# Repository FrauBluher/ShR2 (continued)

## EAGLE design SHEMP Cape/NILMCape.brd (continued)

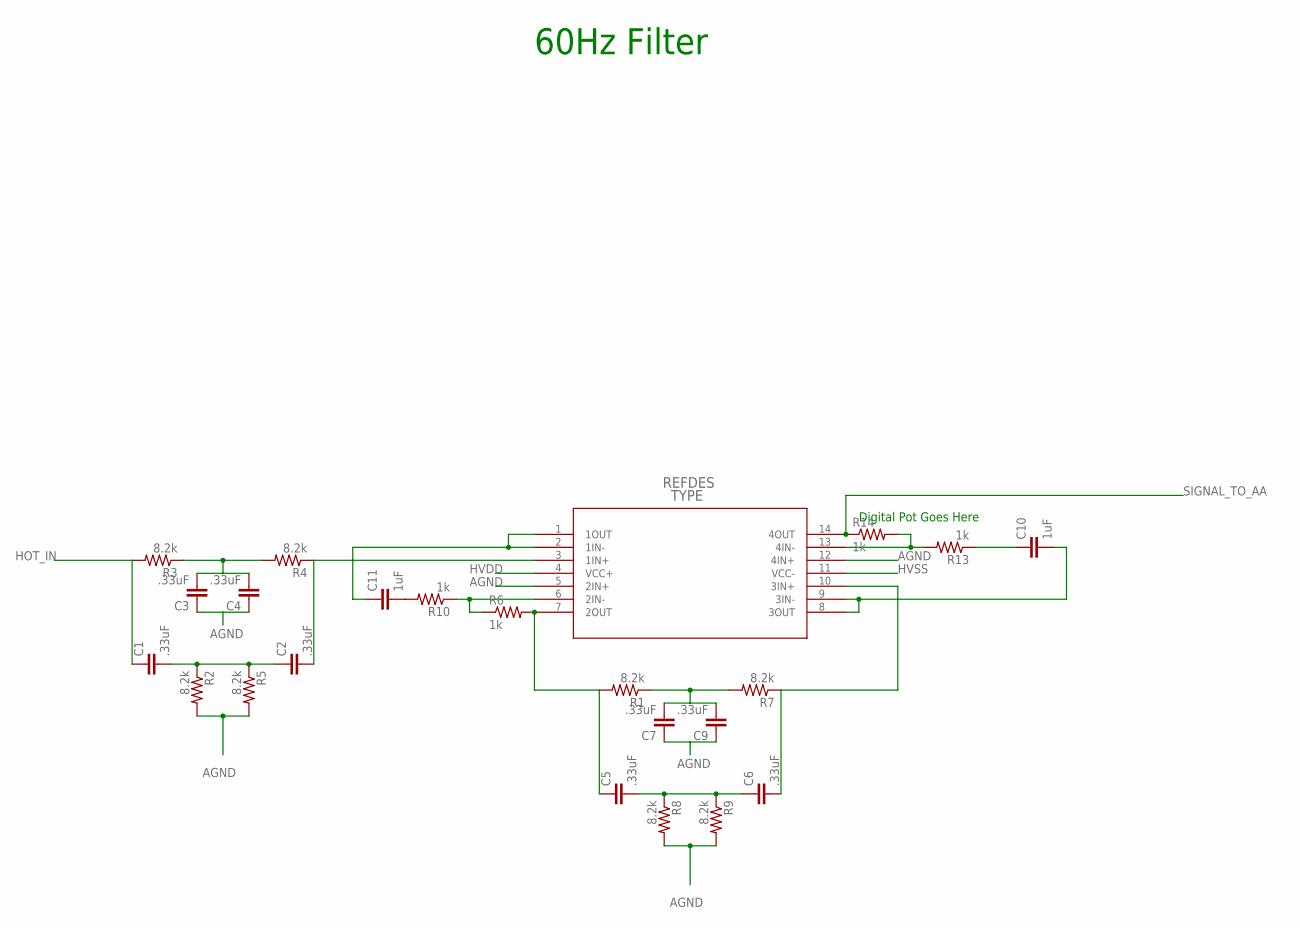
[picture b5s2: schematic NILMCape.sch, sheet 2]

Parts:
C1, C2, C3, C4, C5, C6, C7, C9: .33uF; 0805
C10, C11: 1uF; 0805
R1, R2, R3, R4, R5, R7, R8, R9: 8.2k; 0805
R6, R10, R13, R14: 1k; 0805
U9: TL074_PW_14; PW14

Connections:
AGND: C3.1, C4.1, C7.1, C9.1, R2.2, R5.2, R8.2, R9.2, U9.5 (2IN+), U9.12 (4IN+)
HOT_IN: C1.1, R3.2
HVDD: U9.4 (VCC+)
HVSS: U9.11 (VCC-); also elsewhere on the board
unnamed: C5.1, R1.2, R6.2, U9.7 (2OUT)
unnamed: C1.2, C2.1, R2.1, R5.1
unnamed: C3.2, C4.2, R3.1, R4.2
unnamed: R6.1, R10.1, U9.6 (2IN-)
unnamed: C2.2, R4.1, U9.3 (1IN+)
unnamed: C5.2, C6.1, R8.1, R9.1
unnamed: C7.2, C9.2, R1.1, R7.2
unnamed: C6.2, R7.1, U9.10 (3IN+)
unnamed: C10.2, U9.8 (3OUT), U9.9 (3IN-)
unnamed: R13.2, R14.2, U9.13 (4IN-)
unnamed: C10.1, R13.1
unnamed: C11.2, R10.2
unnamed: C11.1, U9.1 (1OUT), U9.2 (1IN-)
SIGNAL_TO_AA: R14.1, U9.14 (4OUT)

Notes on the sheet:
60Hz Filter
Digital Pot Goes Here

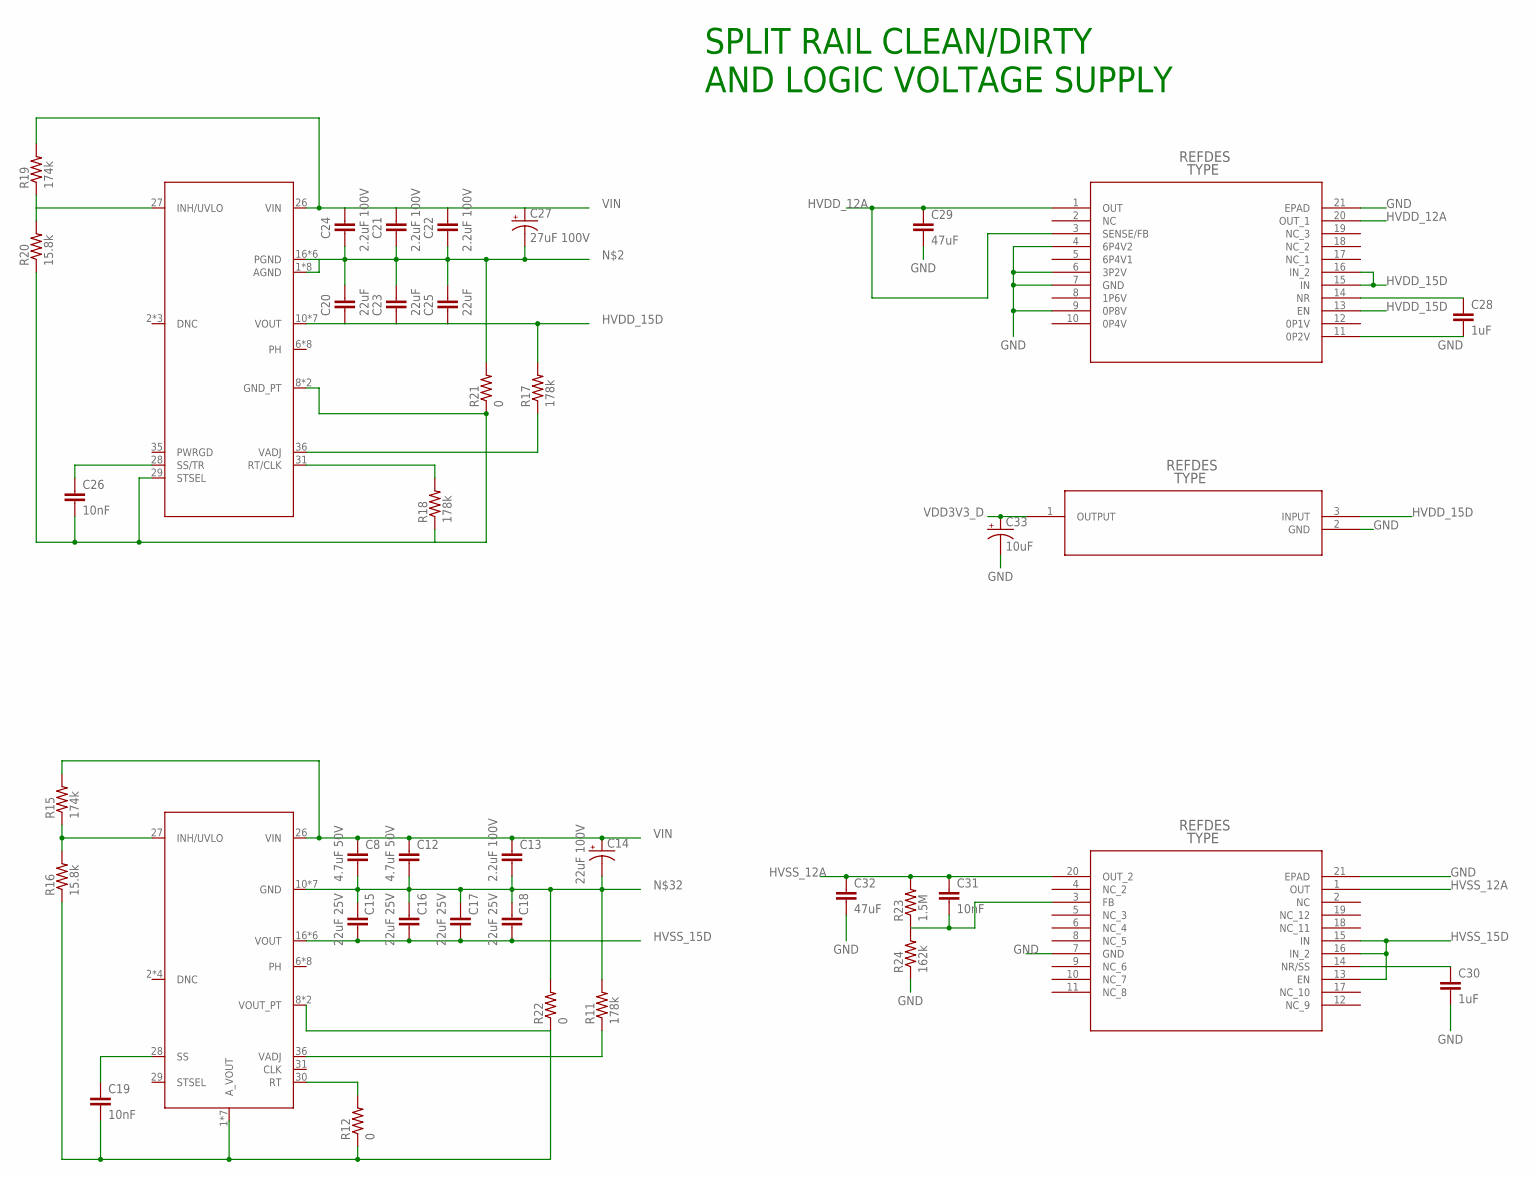
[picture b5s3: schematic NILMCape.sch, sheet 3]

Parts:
C8, C12: 4.7uF 50V; 1210
C13, C21, C22, C24: 2.2uF 100V; 1210
C14: 22uF 100V; CPOL-RADIAL-100UF-25V
C15, C16, C17, C18: 22uF 25V; 1210
C19, C26, C31: 10nF; 0805
C20, C23, C25: 22uF; 1210
C27: 27uF 100V; CPOL-RADIAL-100UF-25V
C28, C30: 1uF; 0805
C29, C32: 47uF; 1210
C33: 10uF; CPOL-RADIAL-10UF-25V
R11, R17, R18: 178k; 0805
R12, R21, R22: 0; 0805
R15, R19: 174k; 0805
R16, R20: 15.8k; 0805
R23: 1.5M; 0805
R24: 162k; 0805
U5: TPS84250_RKG_41; RKG41
U6: TPS7A3301_RGW_20; RGW20_3P15X3P15
U7: LP2950-33_KVU_3; KVU3
U$2: TPS84259_RKG_41; RKG41
U$3: TPS7A4700_RGW_20; RGW20_3P15X3P15

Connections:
GND: C19.2, C28.2, C29.2, C30.2, C32.2, C33.2 (-), R12.1, R16.1, R22.1, R24.1, U6.7 (GND), U6.21 (EPAD), U7.2 (GND), U$2.1 (A_VOUT), U$2.4 (A_VOUT), U$2.5 (A_VOUT), U$2.8 (VOUT_PT), U$2.9 (VOUT_PT), U$2.32 (A_VOUT), U$2.33 (A_VOUT), U$2.34 (A_VOUT), U$2.37 (A_VOUT), U$3.4 (6P4V2), U$3.6 (3P2V), U$3.7 (GND), U$3.9 (0P8V), U$3.11 (0P2V), U$3.21 (EPAD); also elsewhere on the board
HVDD_12A: C29.1, U$3.1 (OUT), U$3.3 (SENSE/FB), U$3.20 (OUT_1)
HVDD_15D: C20.2, C23.2, C25.2, R17.2, U5.10 (VOUT), U5.11 (VOUT), U5.12 (VOUT), U5.13 (VOUT), U5.14 (VOUT), U5.15 (VOUT), U5.39 (VOUT), U7.3 (INPUT), U$3.13 (EN), U$3.15 (IN), U$3.16 (IN_2)
HVSS_12A: C31.1, C32.1, R23.2, U6.1 (OUT), U6.20 (OUT_2)
HVSS_15D: C15.2, C16.2, C17.2, C18.2, U6.13 (EN), U6.15 (IN), U6.16 (IN_2), U$2.16 (VOUT), U$2.17 (VOUT), U$2.18 (VOUT), U$2.19 (VOUT), U$2.20 (VOUT), U$2.40 (VOUT)
unnamed: C20.1, C21.2, C22.2, C23.1, C24.2, C25.1, C27.2 (-), R21.2, U5.1 (AGND), U5.4 (AGND), U5.5 (AGND), U5.16 (PGND), U5.17 (PGND), U5.18 (PGND), U5.19 (PGND), U5.20 (PGND), U5.30 (AGND), U5.32 (AGND), U5.33 (AGND), U5.34 (AGND), U5.37 (AGND), U5.40 (PGND)
unnamed: C19.1, U$2.28 (SS)
unnamed: C31.2, R24.2, U6.3 (FB)
unnamed: R11.1, U$2.36 (VADJ)
unnamed: R12.2, U$2.30 (RT)
unnamed: C8.2, C12.2, C13.2, C14.2 (-), C15.1, C16.1, C17.1, C18.1, R11.2, R22.2, U$2.10 (GND), U$2.11 (GND), U$2.12 (GND), U$2.13 (GND), U$2.14 (GND), U$2.15 (GND), U$2.39 (GND)
unnamed: C30.1, U6.14 (NR/SS)
unnamed: R15.1, R16.2, U$2.27 (INH/UVLO)
unnamed: R17.1, U5.36 (VADJ)
unnamed: R18.2, U5.31 (RT/CLK)
unnamed: R19.1, R20.2, U5.27 (INH/UVLO)
unnamed: C26.1, U5.28 (SS/TR)
unnamed: C26.2, R18.1, R20.1, R21.1, U5.8 (GND_PT), U5.9 (GND_PT), U5.29 (STSEL)
unnamed: C28.1, U$3.14 (NR)
VDD3V3_D: C33.1 (+), U7.1 (OUTPUT); also elsewhere on the board
VIN: C8.1, C12.1, C13.1, C14.1 (+), C21.1, C22.1, C24.1, C27.1 (+), R15.2, R19.2, U5.26 (VIN), U$2.26 (VIN)

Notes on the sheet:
SPLIT RAIL CLEAN/DIRTY AND LOGIC VOLTAGE SUPPLY

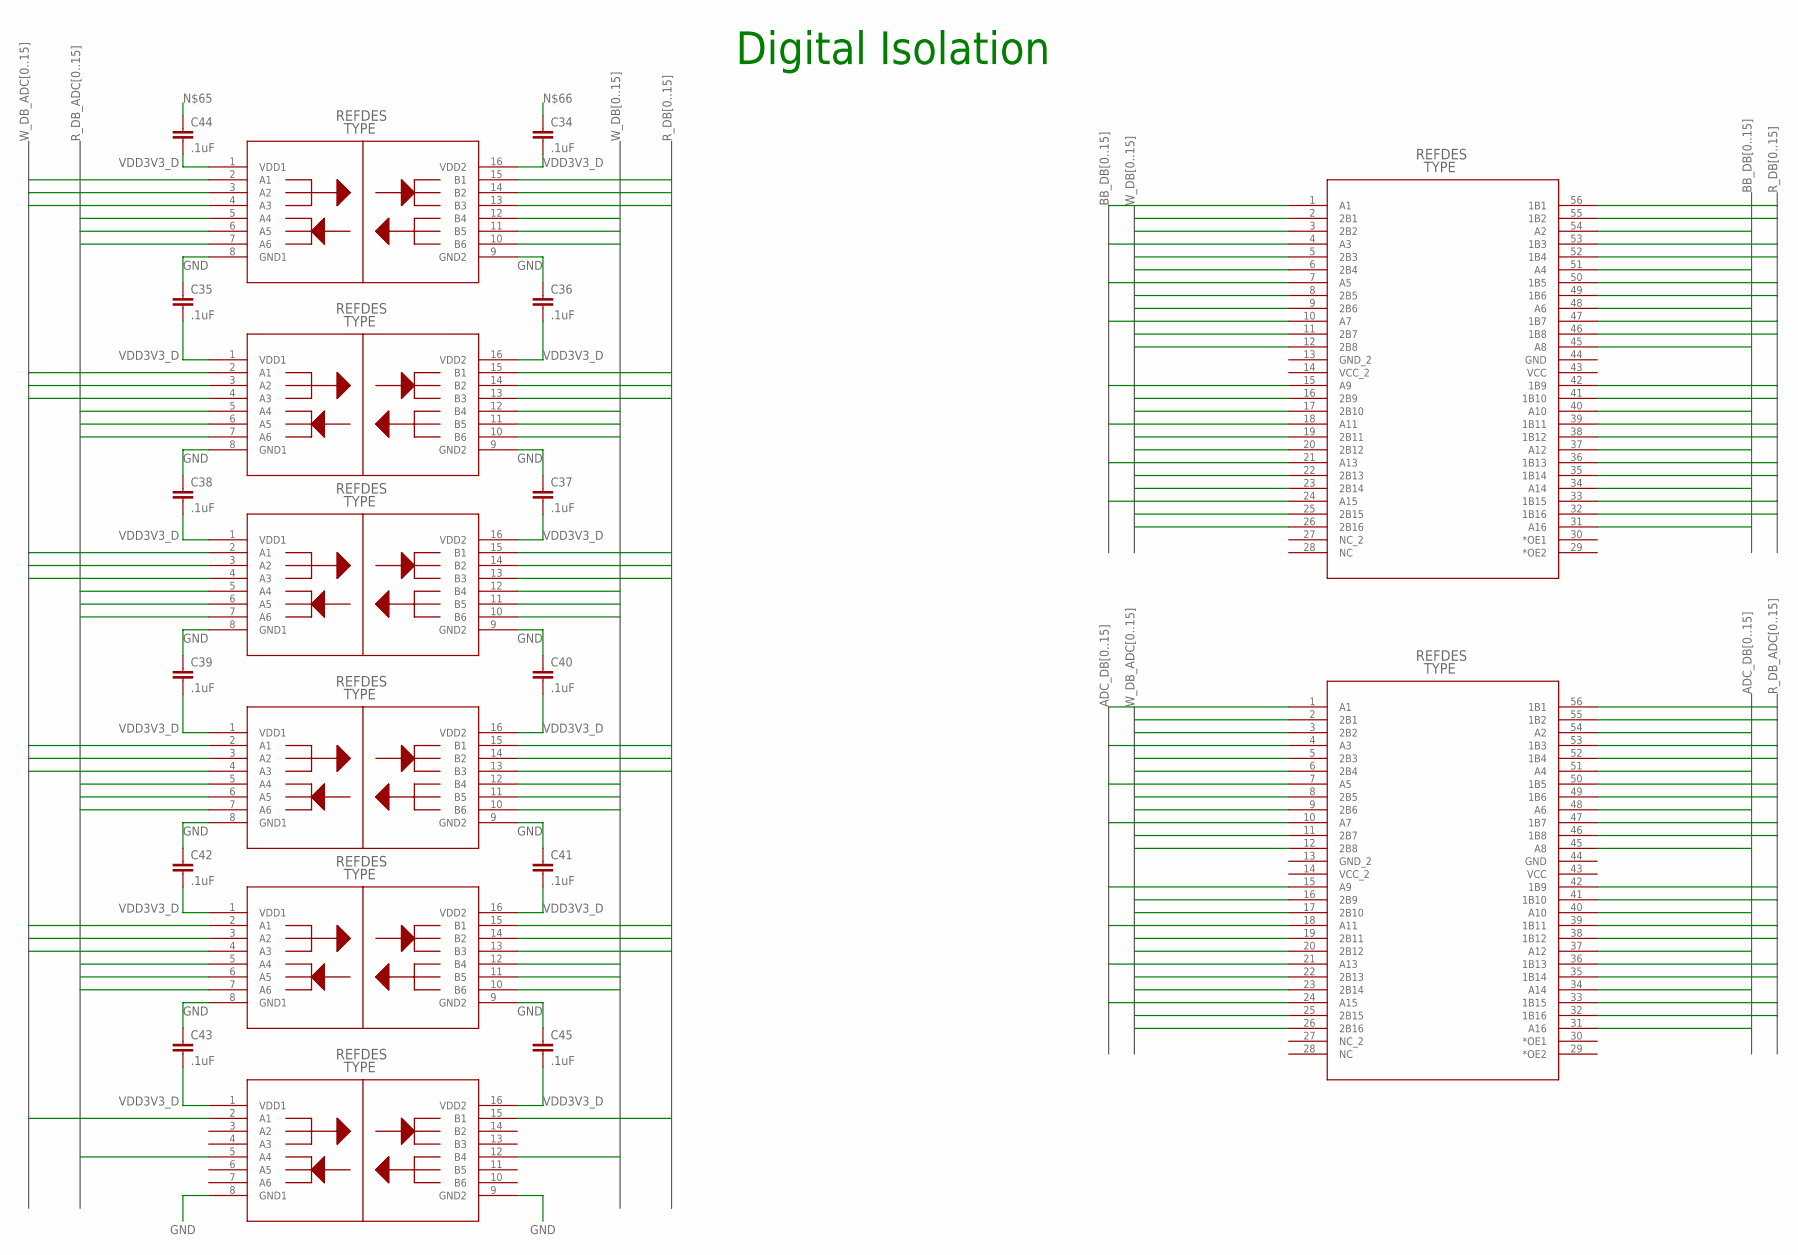
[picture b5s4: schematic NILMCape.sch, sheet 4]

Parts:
C34, C35, C36, C37, C38, C39, C40, C41, C42, C43, C44, C45: .1uF; 0805
U3, U8, U10, U11, U12, U13: SI8663BC-B-IS1; SOIC-16
U4, U14: SN74CBT16390_DGG; DGG56

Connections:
ADC_DB0: U14.1 (A1); also elsewhere on the board
ADC_DB1: U14.54 (A2); also elsewhere on the board
ADC_DB2: U14.4 (A3); also elsewhere on the board
ADC_DB3: U14.51 (A4); also elsewhere on the board
ADC_DB4: U14.7 (A5); also elsewhere on the board
ADC_DB5: U14.48 (A6); also elsewhere on the board
ADC_DB6: U14.10 (A7); also elsewhere on the board
ADC_DB7: U14.45 (A8); also elsewhere on the board
ADC_DB8: U14.15 (A9); also elsewhere on the board
ADC_DB9: U14.40 (A10); also elsewhere on the board
ADC_DB10: U14.18 (A11); also elsewhere on the board
ADC_DB11: U14.37 (A12); also elsewhere on the board
ADC_DB12: U14.21 (A13); also elsewhere on the board
ADC_DB13: U14.34 (A14); also elsewhere on the board
ADC_DB14: U14.24 (A15); also elsewhere on the board
ADC_DB15: U14.31 (A16); also elsewhere on the board
BB_DB0: U4.1 (A1); also elsewhere on the board
BB_DB1: U4.54 (A2); also elsewhere on the board
BB_DB2: U4.4 (A3); also elsewhere on the board
BB_DB3: U4.51 (A4); also elsewhere on the board
BB_DB4: U4.7 (A5); also elsewhere on the board
BB_DB5: U4.48 (A6); also elsewhere on the board
BB_DB6: U4.10 (A7); also elsewhere on the board
BB_DB7: U4.45 (A8); also elsewhere on the board
BB_DB8: U4.15 (A9); also elsewhere on the board
BB_DB9: U4.40 (A10); also elsewhere on the board
BB_DB10: U4.18 (A11); also elsewhere on the board
BB_DB11: U4.37 (A12); also elsewhere on the board
BB_DB12: U4.21 (A13); also elsewhere on the board
BB_DB13: U4.34 (A14); also elsewhere on the board
BB_DB14: U4.24 (A15); also elsewhere on the board
BB_DB15: U4.31 (A16); also elsewhere on the board
GND: C35.1, C36.1, C37.1, C38.1, C39.1, C40.1, C41.1, C42.1, C43.1, C45.1, U3.8 (GND1), U3.9 (GND2), U8.8 (GND1), U8.9 (GND2), U10.8 (GND1), U10.9 (GND2), U11.8 (GND1), U11.9 (GND2), U12.8 (GND1), U12.9 (GND2), U13.8 (GND1), U13.9 (GND2); also elsewhere on the board
R_DB0: U4.56 (1B1), U12.15 (B1)
R_DB1: U4.55 (1B2), U12.14 (B2)
R_DB2: U4.53 (1B3), U12.13 (B3)
R_DB3: U4.52 (1B4), U11.15 (B1)
R_DB4: U4.50 (1B5), U11.14 (B2)
R_DB5: U4.49 (1B6), U11.13 (B3)
R_DB6: U4.47 (1B7), U10.15 (B1)
R_DB7: U4.46 (1B8), U10.14 (B2)
R_DB8: U4.42 (1B9), U10.13 (B3)
R_DB9: U3.15 (B1), U4.41 (1B10)
R_DB10: U3.14 (B2), U4.39 (1B11)
R_DB11: U3.13 (B3), U4.38 (1B12)
R_DB12: U4.36 (1B13), U8.15 (B1)
R_DB13: U4.35 (1B14), U8.14 (B2)
R_DB14: U4.33 (1B15), U8.13 (B3)
R_DB15: U4.32 (1B16), U13.15 (B1)
R_DB_ADC0: U12.5 (A4), U14.56 (1B1)
R_DB_ADC1: U12.6 (A5), U14.55 (1B2)
R_DB_ADC2: U12.7 (A6), U14.53 (1B3)
R_DB_ADC3: U11.5 (A4), U14.52 (1B4)
R_DB_ADC4: U11.6 (A5), U14.50 (1B5)
R_DB_ADC5: U11.7 (A6), U14.49 (1B6)
R_DB_ADC6: U10.5 (A4), U14.47 (1B7)
R_DB_ADC7: U10.6 (A5), U14.46 (1B8)
R_DB_ADC8: U10.7 (A6), U14.42 (1B9)
R_DB_ADC9: U3.5 (A4), U14.41 (1B10)
R_DB_ADC10: U3.6 (A5), U14.39 (1B11)
R_DB_ADC11: U3.7 (A6), U14.38 (1B12)
R_DB_ADC12: U8.5 (A4), U14.36 (1B13)
R_DB_ADC13: U8.6 (A5), U14.35 (1B14)
R_DB_ADC14: U8.7 (A6), U14.33 (1B15)
R_DB_ADC15: U13.5 (A4), U14.32 (1B16)
VDD3V3_D: C34.2, C35.2, C36.2, C37.2, C38.2, C39.2, C40.2, C41.2, C42.2, C43.2, C44.2, C45.2, U3.1 (VDD1), U3.16 (VDD2), U8.1 (VDD1), U8.16 (VDD2), U10.1 (VDD1), U10.16 (VDD2), U11.1 (VDD1), U11.16 (VDD2), U12.1 (VDD1), U12.16 (VDD2), U13.1 (VDD1), U13.16 (VDD2); also elsewhere on the board
W_DB0: U4.2 (2B1), U12.12 (B4)
W_DB1: U4.3 (2B2), U12.11 (B5)
W_DB2: U4.5 (2B3), U12.10 (B6)
W_DB3: U4.6 (2B4), U11.12 (B4)
W_DB4: U4.8 (2B5), U11.11 (B5)
W_DB5: U4.9 (2B6), U11.10 (B6)
W_DB6: U4.11 (2B7), U10.12 (B4)
W_DB7: U4.12 (2B8), U10.11 (B5)
W_DB8: U4.16 (2B9), U10.10 (B6)
W_DB9: U3.12 (B4), U4.17 (2B10)
W_DB10: U3.11 (B5), U4.19 (2B11)
W_DB11: U3.10 (B6), U4.20 (2B12)
W_DB12: U4.22 (2B13), U8.12 (B4)
W_DB13: U4.23 (2B14), U8.11 (B5)
W_DB14: U4.25 (2B15), U8.10 (B6)
W_DB15: U4.26 (2B16), U13.12 (B4)
W_DB_ADC0: U12.2 (A1), U14.2 (2B1)
W_DB_ADC1: U12.3 (A2), U14.3 (2B2)
W_DB_ADC2: U12.4 (A3), U14.5 (2B3)
W_DB_ADC3: U11.2 (A1), U14.6 (2B4)
W_DB_ADC4: U11.3 (A2), U14.8 (2B5)
W_DB_ADC5: U14.9 (2B6)
W_DB_ADC6: U10.2 (A1), U11.4 (A3), U14.11 (2B7)
W_DB_ADC7: U10.3 (A2), U14.12 (2B8)
W_DB_ADC8: U10.4 (A3), U14.16 (2B9)
W_DB_ADC9: U3.2 (A1), U14.17 (2B10)
W_DB_ADC10: U3.3 (A2), U14.19 (2B11)
W_DB_ADC11: U3.4 (A3), U14.20 (2B12)
W_DB_ADC12: U8.2 (A1), U14.22 (2B13)
W_DB_ADC13: U8.3 (A2), U14.23 (2B14)
W_DB_ADC14: U8.4 (A3), U14.25 (2B15)
W_DB_ADC15: U13.2 (A1), U14.26 (2B16)

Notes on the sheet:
Digital Isolation

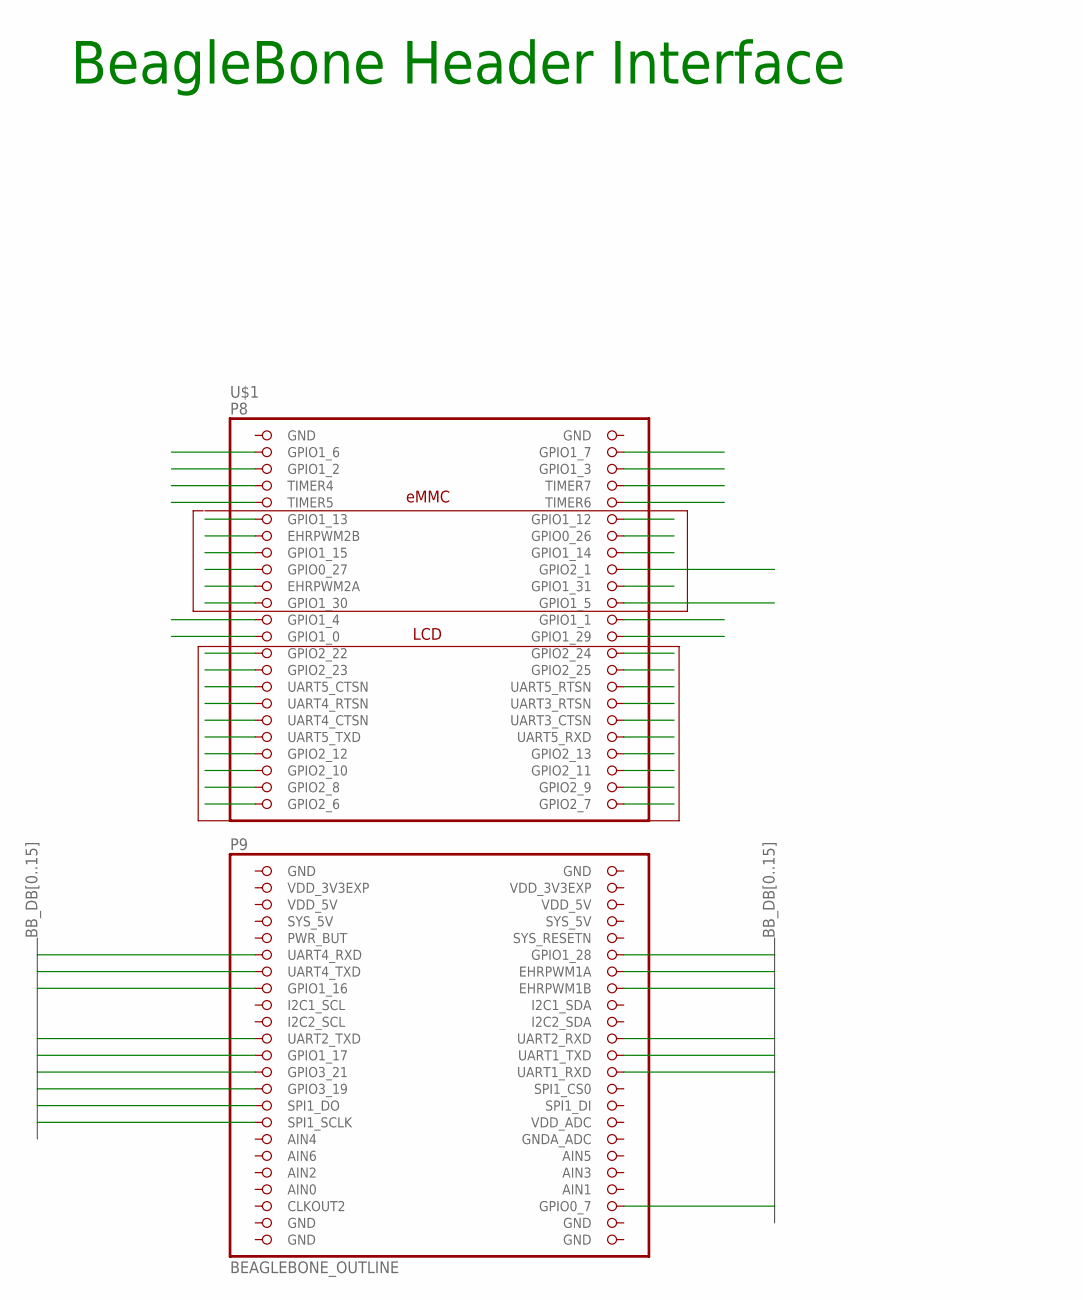
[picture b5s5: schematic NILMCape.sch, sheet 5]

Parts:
U$1: BEAGLEBONE_OUTLINE; BEAGLEBONE_SHIELD

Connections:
AIN0: U$1.85 (AIN0)
BB_DB0: U$1.57 (UART4_RXD); also elsewhere on the board
BB_DB1: U$1.59 (UART4_TXD); also elsewhere on the board
BB_DB2: U$1.61 (GPIO1_16); also elsewhere on the board
BB_DB3: U$1.67 (UART2_TXD); also elsewhere on the board
BB_DB4: U$1.69 (GPIO1_17); also elsewhere on the board
BB_DB5: U$1.71 (GPIO3_21); also elsewhere on the board
BB_DB6: U$1.73 (GPIO3_19); also elsewhere on the board
BB_DB7: U$1.75 (SPI1_DO); also elsewhere on the board
BB_DB8: U$1.77 (SPI1_SCLK); also elsewhere on the board
BB_DB9: U$1.58 (GPIO1_28); also elsewhere on the board
BB_DB10: U$1.60 (EHRPWM1A); also elsewhere on the board
BB_DB11: U$1.62 (EHRPWM1B); also elsewhere on the board
BB_DB12: U$1.68 (UART2_RXD); also elsewhere on the board
BB_DB13: U$1.70 (UART1_TXD); also elsewhere on the board
BB_DB14: U$1.72 (UART1_RXD); also elsewhere on the board
BB_DB15: U$1.88 (GPIO0_7); also elsewhere on the board
GND: U$1.1 (GND), U$1.2 (GND), U$1.47 (GND), U$1.48 (GND), U$1.89 (GND), U$1.90 (GND), U$1.91 (GND), U$1.92 (GND); also elsewhere on the board
SYS_5V: U$1.53 (SYS_5V)
VDD_3V3EXP: U$1.49 (VDD_3V3EXP), U$1.50 (VDD_3V3EXP)
VDD_5V: U$1.51 (VDD_5V), U$1.52 (VDD_5V)

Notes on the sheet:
eMMC
LCD
BeagleBone Header Interface

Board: 2 copper layers, 88 parts (0 on the bottom side), 135 nets, no tracks yet.

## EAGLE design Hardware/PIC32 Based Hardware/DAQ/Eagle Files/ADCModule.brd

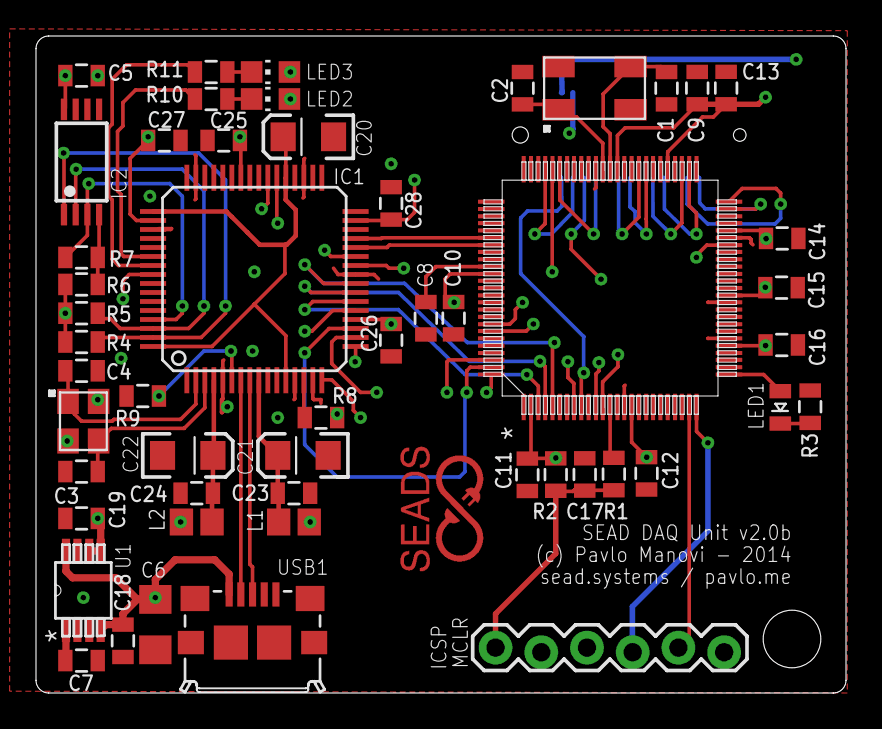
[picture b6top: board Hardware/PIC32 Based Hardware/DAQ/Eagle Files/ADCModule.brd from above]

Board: 4 copper layers, 45.0 x 36.5 mm, 53 parts (1 on the bottom side), 54 nets.

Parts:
C1, C2, C3, C4: 20pF; 0805
C5, C9, C10, C11, C12, C13, C14, C15, C16, C17, C23, C24, C25, C26, C27, C28: .1uF; 0805
C6: 100uF; 1206
C7: .01uF; 0805
C8: 10uF; 0805
C18: 2.2uF; 0805
C19: 4.7uF; 0805
C20: 3.3uF; EIA3216
C21, C22: 4.7uF; EIA3216
IC1: LQFP64
IC2: 93-C46AST; TSSOP8
JP6: 1X06-SIP_LOCK
L1, L2: FB805
LED1: LED-0805
LED2, LED3: CHIP-LED0805
R1, R10, R11: 470; 0805
R2, R4, R5, R6, R8: 10k; 0805
R3: 330; 0805
R7: 2.2k; 0805
R9: 12k 1%; 0805
U1: LP2989_DGK_8; MUA08A
U$1: PIC32MX795F512L-; TQFP100_12X12MC
U$2: ABM3B-8.000MHZ-10-1-U-T; ABM3B
U$3: 7M-12.000MEEQ-T; 7M-CRYSTAL
USB1: CON-USB-F-MICRO-B; CONN_USB_MICRO-B
X1: 52885-0374

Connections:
A0: IC1.27, U$1.44
CS*: IC1.26, U$1.71
D0: IC1.16, U$1.93
D1: IC1.17, U$1.94
D2: IC1.18, U$1.98
D3: IC1.19, U$1.99
D4: IC1.21, U$1.100
D5: IC1.22, U$1.3
D6: IC1.23, U$1.4
D7: IC1.24, U$1.5
GND: C1.2, C2.1, C3.2, C4.1, C5.2, C6.1, C7.1, C8.1, C9.1, C10.1, C11.1, C12.1, C13.1, C14.1, C15.1, C16.1, C17.2, C18.2, C19.1, C20.C, C21.C, C22.C, C23.2, C24.2, C25.1, C26.1, C27.1, C28.1, IC1.1, IC1.5, IC1.10, IC1.11, IC1.13, IC1.15, IC1.25, IC1.35, IC1.47, IC1.51, IC2.5, JP6.3, R3.2, R9.2, U1.3, U$1.15, U$1.31, U$1.36, U$1.45, U$1.65, U$1.75, U$2.2, U$2.4, U$3.2, U$3.4, USB1.P5, X1.1, X1.2, X1.12, X1.18, X1.24, X1.29, X1.30
MCLR: C17.1, JP6.1, R1.1, R2.1
MISO: U$1.9, X1.4
MOSI: U$1.72, X1.6
unnamed: C1.1, U$1.63, U$2.3
unnamed: C2.2, U$1.64, U$2.1
unnamed: C8.2, U$1.85
unnamed: C3.1, IC1.3, U$3.3
unnamed: C4.2, IC1.2, U$3.1
unnamed: IC1.7, USB1.P2
unnamed: IC1.8, USB1.P3
unnamed: IC1.63, IC2.1, R4.1
unnamed: IC1.62, IC2.2, R5.1
unnamed: R1.2, U$1.13
unnamed: LED1.1, U$1.26
unnamed: LED1.2, R3.1
unnamed: IC2.4, R6.1, R7.1
unnamed: IC1.61, IC2.3, R7.2
unnamed: IC1.14, R8.1
unnamed: IC1.6, R9.1
unnamed: C22.A, C24.1, IC1.4, L2.1
unnamed: C21.A, C23.1, IC1.9, L1.1
unnamed: C7.2, U1.1
unnamed: IC1.54, R10.2
unnamed: IC1.55, R11.2
unnamed: LED2.C, R10.1
unnamed: LED3.C, R11.1
PGC: JP6.5, U$1.24
PGD: JP6.4, U$1.25
RD*: IC1.28, U$1.82
SCK: U$1.70, X1.10
SCL: U$1.58, X1.16
SDA: U$1.59, X1.14
SS: U$1.8, X1.8
U1RX: U$1.52, X1.22
U1TX: U$1.53, X1.20
U3RX: U$1.49, X1.28
U3TX: U$1.50, X1.26
USB_UART_RX: IC1.39, U$1.12
USB_UART_TX: IC1.38, U$1.11
VCC1V8_D: C20.A, IC1.12, IC1.37, IC1.49, IC1.64
VDD3V3_D: C5.1, C9.2, C10.2, C11.2, C12.2, C13.2, C14.2, C15.2, C16.2, C19.2, C25.2, C26.2, C27.2, C28.2, IC1.20, IC1.31, IC1.42, IC1.50, IC1.56, IC2.8, JP6.2, L1.2, L2.2, LED2.A, LED3.A, R2.2, R4.2, R5.2, R6.2, R8.2, U1.5, U1.6, U$1.2, U$1.16, U$1.30, U$1.37, U$1.46, U$1.55, U$1.62, U$1.86, X1.5
VDD5V0_D: C6.2, C18.1, U1.4, U1.8, USB1.P1, X1.3
WR*: IC1.29, U$1.81

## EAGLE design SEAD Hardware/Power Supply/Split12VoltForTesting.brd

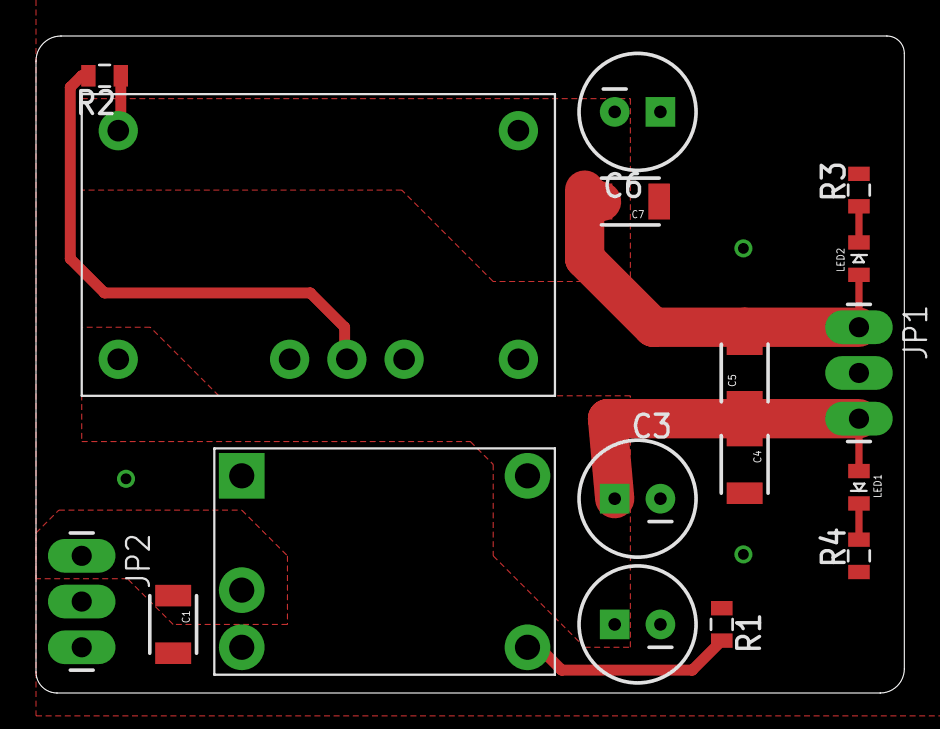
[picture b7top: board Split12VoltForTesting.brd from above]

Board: 2 copper layers, 48.2 x 36.5 mm, 17 parts (0 on the bottom side), 8 nets.

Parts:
C1, C4, C5, C7: 2.2uF; 1210
C2, C3, C6: 100uF; CPOL-RADIAL-100UF-25V
JP1, JP2: M03LONGPADS; 1X03_LONGPADS
LED1, LED2: LED-0805
R1: 14.9k; 0805
R2: 100; 0805
R3, R4: 1.5k; 0805
U$1: PTN78000THROUGH-HOLE; PTN78000
U$2: PTN78060A; PTN_EUW

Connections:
GND: C1.2, C2.2, C3.2, C4.2, C6.1, C7.1, JP1.2, JP2.2, JP2.3, R1.1, R3.2, R4.1, U$1.GND, U$2.6
unnamed: LED2.2, R3.1
unnamed: R2.2, U$2.4
unnamed: R1.2, U$1.ADJ
unnamed: LED1.2, R4.2
VDD15V0_D: C2.1, C3.1, C4.1, C5.1, JP1.3, LED1.1, U$1.V_OUT, U$2.2
VSS15V0_D: C5.2, C6.2, C7.2, JP1.1, LED2.1, R2.1, U$2.1, U$2.7
V_IN: C1.1, JP2.1, U$1.V_IN

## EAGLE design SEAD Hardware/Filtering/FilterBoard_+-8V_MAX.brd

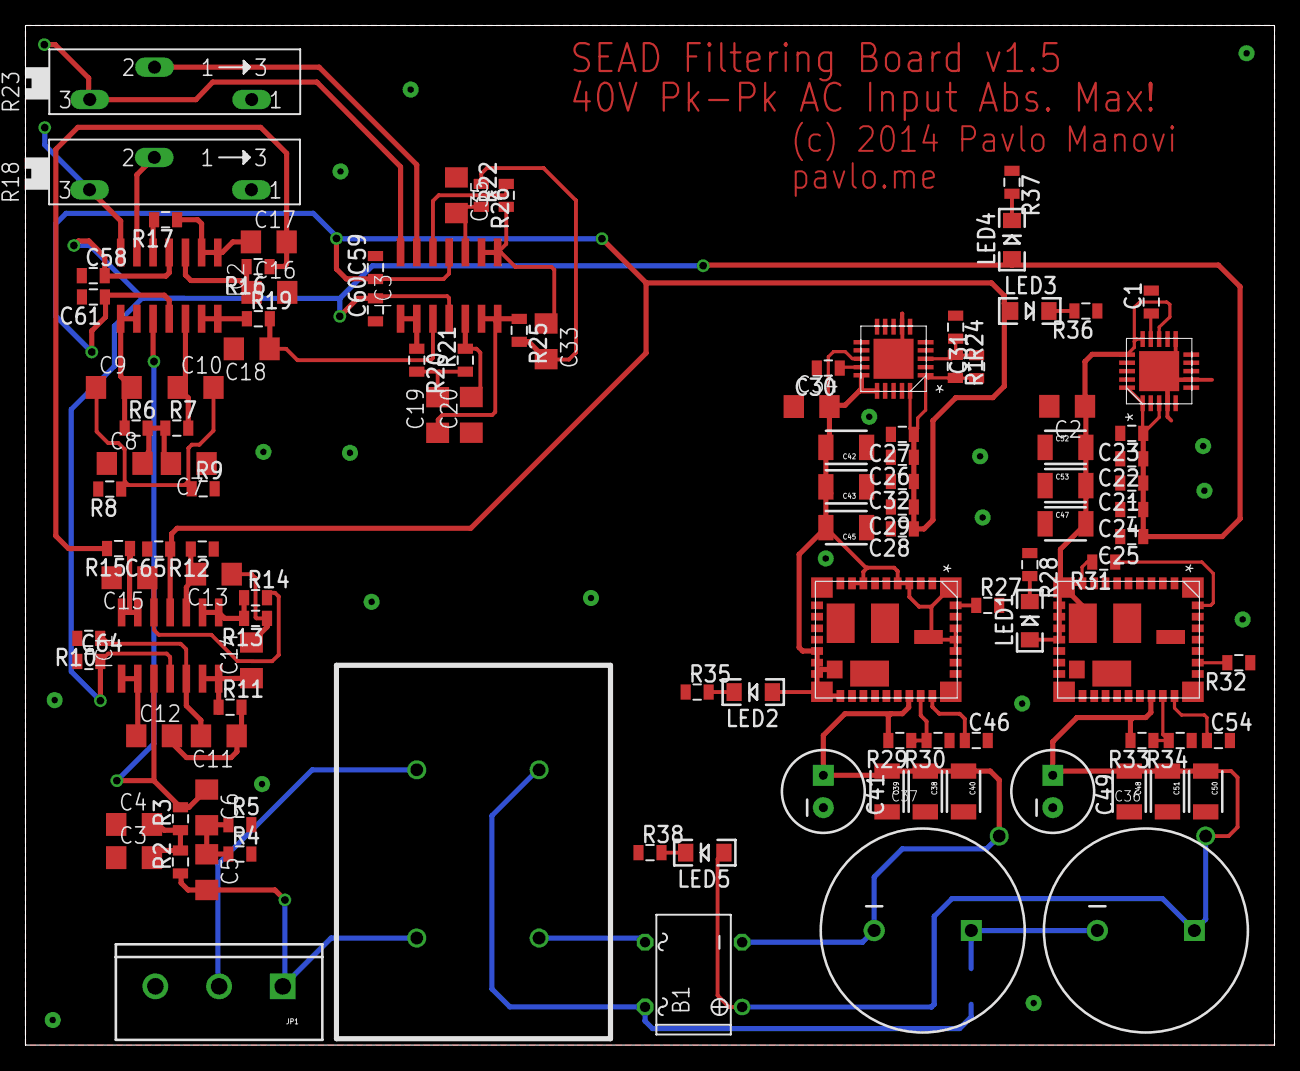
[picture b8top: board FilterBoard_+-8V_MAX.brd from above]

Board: 2 copper layers, 98.0 x 80.0 mm, 112 parts (1 on the bottom side), 58 nets.

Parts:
B1: B-DIL
C1, C30: 1uF; 0805
C2, C34: 10uF; 1206
C3, C4, C5, C6, C7, C8, C9, C10: 22nF; 1206
C11, C12, C13, C14, C15, C16, C17, C18, C19, C20, C33, C35: 1206
C21, C22, C23, C24, C25, C26, C27, C28, C29, C32: 10uF; 0805
C31, C46, C54, C58, C59, C60, C61, C64, C65: 10nF; 0805
C36, C37: CPOL-RADIAL-1000UF-63V
C38, C39: 4.7uF 50V; 1210
C40, C48, C50, C51: 2.2uF 100V; 1210
C41: 22uF 100V; CPOL-RADIAL-100UF-25V
C42, C43, C45: 22uF 25V; 1210
C47, C52, C53: 22uF; 1210
C49: 27uF 100V; CPOL-RADIAL-100UF-25V
IC1, IC2, IC3: TL084D; SO14
JP1: M03-SCREW-5MM; SCREWTERMINAL-5MM-3
LED1, LED2, LED3, LED4, LED5: LED-1206
R1: 1.24M; 0805
R2, R3, R4, R5, R6, R7, R8, R9: 121k; 0805
R10, R11, R12, R13, R14, R15, R16, R17, R19, R20, R21, R22, R25, R26, R28, R35, R36, R37, R38: 0805
R18, R23: SP19L
R24: 215k; 0805
R27, R31, R32: 178k; 0805
R29, R33: 174k; 0805
R30, R34: 15.8k; 0805
R39: 0; 1206
U7: TPS7A3301_RGW_20; RGW20_3P15X3P15
U8: TPS84250_RKG_41; RKG41
U$1: TPS84259_RKG_41; RKG41
U$2: TPS7A4700_RGW_20; RGW20_3P15X3P15

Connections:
GND: C1.2, C2.2, C3.1, C4.1, C7.1, C8.1, C15.2, C16.2, C18.2, C20.1, C21.2, C22.2, C23.2, C24.2, C25.2, C26.2, C27.2, C28.2, C29.2, C30.2, C32.2, C34.1, C35.1, C36.2, C37.1, C38.2, C39.2, C40.2, C41.2, C42.1, C43.1, C45.1, C46.2, C47.1, C48.2, C49.2, C50.2, C51.2, C52.1, C53.1, C54.2, C58.1, C59.2, C60.1, C61.2, C64.1, C65.2, R4.2, R5.2, R8.2, R9.2, R10.2, R12.1, R24.1, R27.2, R28.1, R30.1, R32.1, R34.1, R35.1, R36.1, R37.1, R38.1, R39.2, U7.7, U7.21, U8.1, U8.4, U8.5, U8.8, U8.9, U8.16, U8.17, U8.18, U8.19, U8.20, U8.29, U8.30, U8.32, U8.33, U8.34, U8.37, U8.40, U$1.10, U$1.11, U$1.12, U$1.13, U$1.14, U$1.15, U$1.30, U$1.39, U$2.4, U$2.6, U$2.7, U$2.9, U$2.11, U$2.21
HVDD_8A: C21.1, C22.1, C23.1, C24.1, C25.1, C58.2, C60.2, C64.2, IC1.4, IC2.4, IC3.4, LED4.A, U$2.1, U$2.3, U$2.20
HVDD_15D: C2.1, C47.2, C52.2, C53.2, LED1.A, R31.2, U8.10, U8.11, U8.12, U8.13, U8.14, U8.15, U8.39, U$2.13, U$2.15, U$2.16
HVDD_IN: B1.+, C36.1, C48.1, C49.1, C50.1, C51.1, LED5.A, R33.2, U8.26
HVSS_8A: C26.1, C27.1, C28.1, C29.1, C31.1, C32.1, C59.1, C61.1, C65.1, IC1.11, IC2.11, IC3.11, LED3.A, R1.2, U7.1, U7.20
HVSS_15D: C34.2, C42.2, C43.2, C45.2, LED2.A, U7.13, U7.15, U7.16, U$1.1, U$1.4, U$1.5, U$1.8, U$1.9, U$1.16, U$1.17, U$1.18, U$1.19, U$1.20, U$1.32, U$1.33, U$1.34, U$1.37, U$1.40
HVSS_IN: B1.-, C37.2, C38.1, C39.1, C40.1, C41.1, R29.2, U$1.26
unnamed: C1.1, U$2.14
unnamed: C3.2, C4.2, R2.2, R3.1
unnamed: C9.2, IC2.8, IC2.9, R6.1
unnamed: C33.1, IC3.8, IC3.9, R22.1
unnamed: C5.1, C6.2, R4.1, R5.1
unnamed: C7.2, C8.2, R6.2, R7.1
unnamed: C6.1, IC1.3, IC2.10, R3.2
unnamed: C31.2, R1.1, R24.2, U7.3
unnamed: C9.1, C10.2, R8.1, R9.1
unnamed: C10.1, IC2.12, R7.2
unnamed: C12.1, IC1.1, IC1.2
unnamed: C11.1, C12.2, R11.2
unnamed: C11.2, IC1.5, R10.1
unnamed: C14.1, IC1.6, IC1.7, R11.1
unnamed: IC1.8, IC1.9, R13.2, R14.1
unnamed: IC1.13, IC1.14, R15.1
unnamed: C17.1, IC2.1, IC2.2, R17.1
unnamed: IC2.6, R18.S
unnamed: C35.2, IC3.10, R26.2
unnamed: IC3.12, R22.2
unnamed: IC3.13, R23.S
unnamed: C33.2, R25.2, R26.1
unnamed: C19.1, IC3.6, IC3.7, R25.1
unnamed: R27.1, U$1.36
unnamed: C20.2, IC3.5, R21.2
unnamed: C19.2, R20.2, R21.1
unnamed: IC3.1, IC3.2, R20.1
unnamed: C18.1, IC3.3, R19.2
unnamed: LED1.C, R28.2
unnamed: IC2.13, IC2.14, R19.1
unnamed: R29.1, R30.2, U$1.27
unnamed: C30.1, U7.14
unnamed: C46.1, U$1.28
unnamed: C13.1, C14.2, R13.1
unnamed: C13.2, IC1.10, R12.2
unnamed: R31.1, U8.36
unnamed: C15.1, IC1.12, R14.2
unnamed: R32.2, U8.31
unnamed: C17.2, R15.2, R16.1
unnamed: C16.1, IC2.3, R16.2
unnamed: IC2.5, R17.2
unnamed: R33.1, R34.2, U8.27
unnamed: C54.1, U8.28
unnamed: LED2.C, R35.2
unnamed: LED3.C, R36.2
unnamed: LED4.C, R37.2
unnamed: LED5.C, R38.2
OUT_15KHZ: IC3.14, R23.E
OUT_15_100_KHZ: IC2.7, R18.E
VDD_IN: C5.2, JP1.1, R2.1
VDD_L_CHOKE: B1.AC2, R39.1

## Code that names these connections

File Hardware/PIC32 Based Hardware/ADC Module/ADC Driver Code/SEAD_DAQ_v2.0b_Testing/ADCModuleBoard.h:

/**
 * The MIT License (MIT)
 *
 * Copyright (c) 2014 Pavlo Milo Manovi
 *
 * Permission is hereby granted, free of charge, to any person obtaining a copy of
 * this software and associated documentation files (the "Software"), to deal in
 * the Software without restriction, including without limitation the rights to
 * use, copy, modify, merge, publish, distribute, sublicense, and/or sell copies of
 * the Software, and to permit persons to whom the Software is furnished to do so,
 * subject to the following conditions:
 *
 * The above copyright notice and this permission notice shall be included in all
 * copies or substantial portions of the Software.
 *
 * THE SOFTWARE IS PROVIDED "AS IS", WITHOUT WARRANTY OF ANY KIND, EXPRESS OR
 * IMPLIED, INCLUDING BUT NOT LIMITED TO THE WARRANTIES OF MERCHANTABILITY, FITNESS
 * FOR A PARTICULAR PURPOSE AND NONINFRINGEMENT. IN NO EVENT SHALL THE AUTHORS OR
 * COPYRIGHT HOLDERS BE LIABLE FOR ANY CLAIM, DAMAGES OR OTHER LIABILITY, WHETHER
 * IN AN ACTION OF CONTRACT, TORT OR OTHERWISE, ARISING FROM, OUT OF OR IN
 * CONNECTION WITH THE SOFTWARE OR THE USE OR OTHER DEALINGS IN THE SOFTWARE.
 *
 */

/**
 * @file	ADS85x8.h
 * @author 	Pavlo Milo Manovi
 * @date	April, 2014
 * @brief 	This library is used to set up the peripherals of the pic and glue
 *              together all of the drivers in the library.
 */

#ifndef ADCMODULEBOARD_H
#define	ADCMODULEBOARD_H

//#define MAX32

#include <xc.h>
#include <stdint.h>
#include "DMA_Transfer.h"
#include "ADS85x8.h"

/**
 * @brief Pound defines for databit latch registers.
 */
#define DB0_LAT     LATDbits.LATD13
#define DB1_LAT     LATDbits.LATD5
#define DB2_LAT     LATFbits.LATF0
#define DB3_LAT     LATFbits.LATF1
#define DB4_LAT     LATGbits.LATG1 
#define DB5_LAT     LATGbits.LATG0 
#define DB6_LAT     LATAbits.LATA6
#define DB7_LAT     LATAbits.LATA7
#define DB8_LAT     LATEbits.LATE0
#define DB9_LAT     LATEbits.LATE1 
#define DB10_LAT    LATGbits.LATG14
#define DB11_LAT    LATGbits.LATG12
#define DB12_LAT    LATGbits.LATG13
#define DB13_LAT    LATEbits.LATE2
#define DB14_LAT    LATEbits.LATE3
#define DB15_LAT    LATEbits.LATE4

/**
 * @brief Pound defines for databit tri-state registers.
 */
#define DB0_TRIS     TRISDbits.TRISD13
#define DB1_TRIS     TRISDbits.TRISD5
#define DB2_TRIS     TRISFbits.TRISF0
#define DB3_TRIS     TRISFbits.TRISF1
#define DB4_TRIS     TRISGbits.TRISG1 
#define DB5_TRIS     TRISGbits.TRISG0 
#define DB6_TRIS     TRISAbits.TRISA6
#define DB7_TRIS     TRISAbits.TRISA7
#define DB8_TRIS     TRISEbits.TRISE0
#define DB9_TRIS     TRISEbits.TRISE1 
#define DB10_TRIS    TRISGbits.TRISG14
#define DB11_TRIS    TRISGbits.TRISG12
#define DB12_TRIS    TRISGbits.TRISG13
#define DB13_TRIS    TRISEbits.TRISE2
#define DB14_TRIS    TRISEbits.TRISE3
#define DB15_TRIS    TRISEbits.TRISE4

/**
 * @brief Pound defines for databit port registers.
 */
#define DB0_PORT     PORTDbits.RD13 
#define DB1_PORT     PORTDbits.RD5 
#define DB2_PORT     PORTFbits.RF0 
#define DB3_PORT     PORTFbits.RF1 
#define DB4_PORT     PORTGbits.RG1 
#define DB5_PORT     PORTGbits.RG0 
#define DB6_PORT     PORTAbits.RA6 
#define DB7_PORT     PORTAbits.RA7 
#define DB8_PORT     PORTEbits.RE0 
#define DB9_PORT     PORTEbits.RE1 
#define DB10_PORT    PORTGbits.RG14
#define DB11_PORT    PORTGbits.RG12
#define DB12_PORT    PORTGbits.RG13
#define DB13_PORT    PORTEbits.RE2 
#define DB14_PORT    PORTEbits.RE3 
#define DB15_PORT    PORTEbits.RE4 

/**
 * @brief SPI tristate registers and SS latch.
 */
#define SPI_SCK_TRIS    TRISDbits.TRISD10
#define SPI_MOSI_TRIS   TRISDbits.TRISD0
#define SPI_MISO_TRIS   TRISCbits.TRISC4
#define SPI_SS_TRIS     TRISCbits.TRISC3
#define SPI_SS_LAT      LATCbits.LATC3

/**
 * @brief ADS85x8 control lines - tristates.
 */
#define BUSY_TRIS   TRISDbits.TRISD14
#define CS_TRIS     TRISFbits.TRISF12
#define RD_TRIS     TRISBbits.TRISB12
#define WR_TRIS     TRISBbits.TRISB13
#define CONV_A_TRIS TRISBbits.TRISB15
#define CONV_B_TRIS TRISBbits.TRISB14
/*
 * #define CONV_C_TRIS 
 * #define CONV_D_TRIS
 * Define these two when you actually start using them.
 */

/**
 * @brief ADS85x8 control lines - latches.
 */
#define BUSY_PORT  PORTDbits.RD14
#define CS_LAT     LATFbits.LATF12
#define RD_LAT     LATBbits.LATB12
#define WR_LAT     LATBbits.LATB13
#define CONV_A_LAT LATBbits.LATB15
#define CONV_B_LAT LATBbits.LATB14
/*
 * #define CONV_C_LAT 
 * #define CONV_D_LAT
 * Define these two when you actually start using them.
 */

/**
 * @brief UART Pins for debugging on Max32
 */
#define UART_TX_TRIS    TRISGbits.TRISG8
#define UART_RX_TRIS    TRISGbits.TRISG7

/*~~~~~~~~~~~~~~~~~~~~~~~~~~~~~~~~~~Methods~~~~~~~~~~~~~~~~~~~~~~~~~~~~~~~~~~~~*/


/**
 * @brief Sets up the board with the peripherals defined in the header.
 */
uint8_t ADCModuleBoard_Init(SampleBuffer *BufferA, SampleBuffer *BufferB, ADS85x8_Info *DS85x8Info);

#endif	/* ADCMODULEBOARD_H */
